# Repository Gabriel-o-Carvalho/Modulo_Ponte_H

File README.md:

# Modulo_Ponte_H
Uma ponte H simples que pode ser utilizada com arduino.

Cuidado: Não conecte o VCC da fonte sem antes garantir que os pinos de sinal estejam com algum nível lógico (alto ou baixo). Caso contrário, se não tiver nenhuma tensão nos pinos IN1 e IN2, a ponte H entrará em curto circuito.

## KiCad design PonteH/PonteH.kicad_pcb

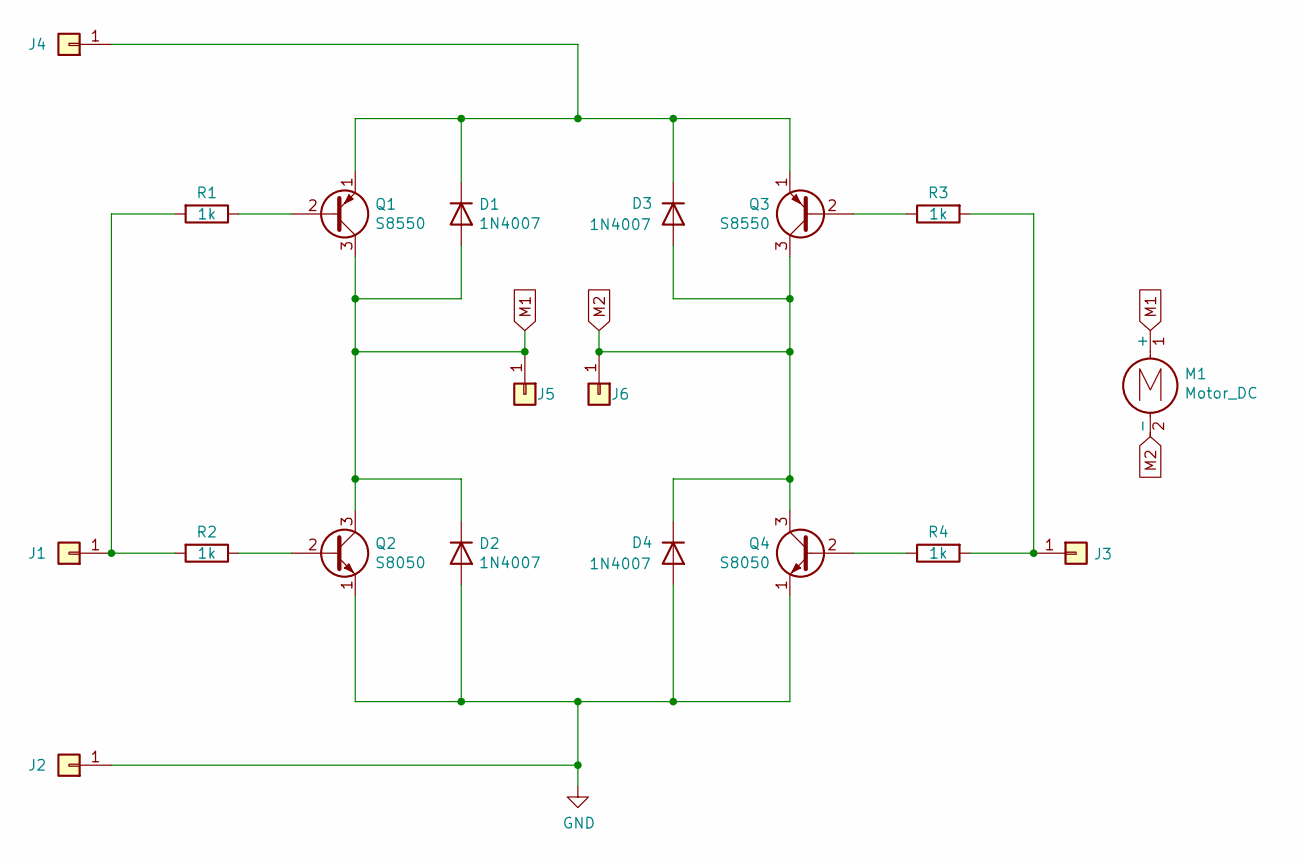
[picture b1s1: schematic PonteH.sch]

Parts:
D1, D2, D3, D4: 1N4007; D_DO-41_SOD81_P10.16mm_Horizontal
J1, J2, J3, J4, J5, J6: Conn_01x01; PinSocket_1x01_P2.54mm_Vertical
M1: Motor_DC
Q1, Q3: S8550; TO-92_Inline
Q2, Q4: S8050; TO-92_Inline
R1, R2, R3, R4: 1k; R_Axial_DIN0207_L6.3mm_D2.5mm_P10.16mm_Horizontal

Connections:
GND: D2.2 (A), D4.2 (A), J2.1, Q2.1 (E), Q4.1 (E)
M1: D1.2 (A), D2.1 (K), J5.1, M1.1 (+), Q1.3 (C), Q2.3 (C)
M2: D3.2 (A), D4.1 (K), J6.1, M1.2 (-), Q3.3 (C), Q4.3 (C)
unnamed: D1.1 (K), D3.1 (K), J4.1, Q1.1 (E), Q3.1 (E)
unnamed: J1.1, R1.2, R2.2
unnamed: J3.1, R3.2, R4.2
unnamed: Q1.2 (B), R1.1
unnamed: Q2.2 (B), R2.1
unnamed: Q3.2 (B), R3.1
unnamed: Q4.2 (B), R4.1

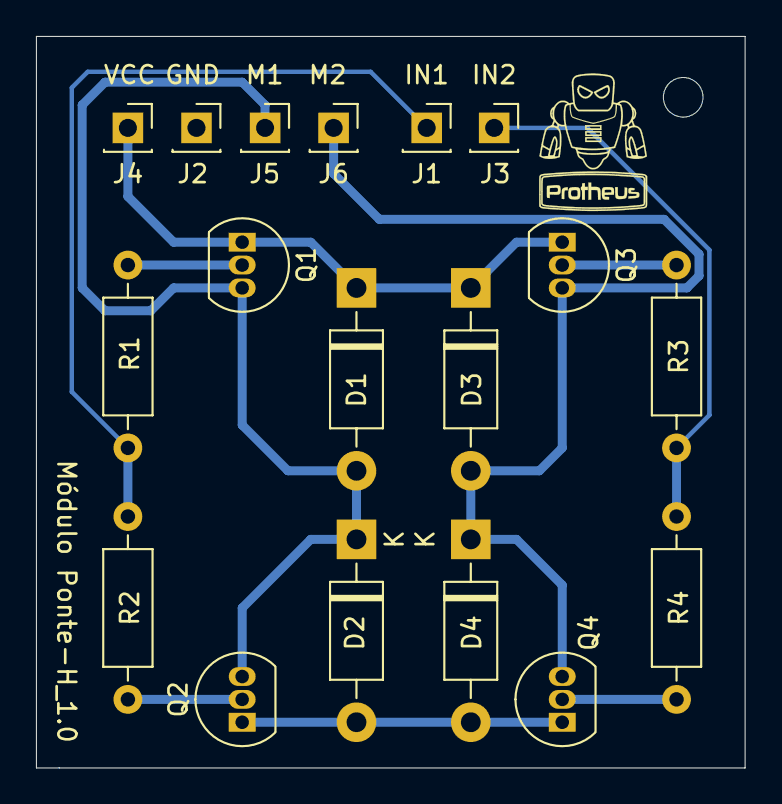
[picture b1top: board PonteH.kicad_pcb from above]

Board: 2 copper layers, 39.4 x 40.6 mm, 18 parts (0 on the bottom side), 10 nets.
